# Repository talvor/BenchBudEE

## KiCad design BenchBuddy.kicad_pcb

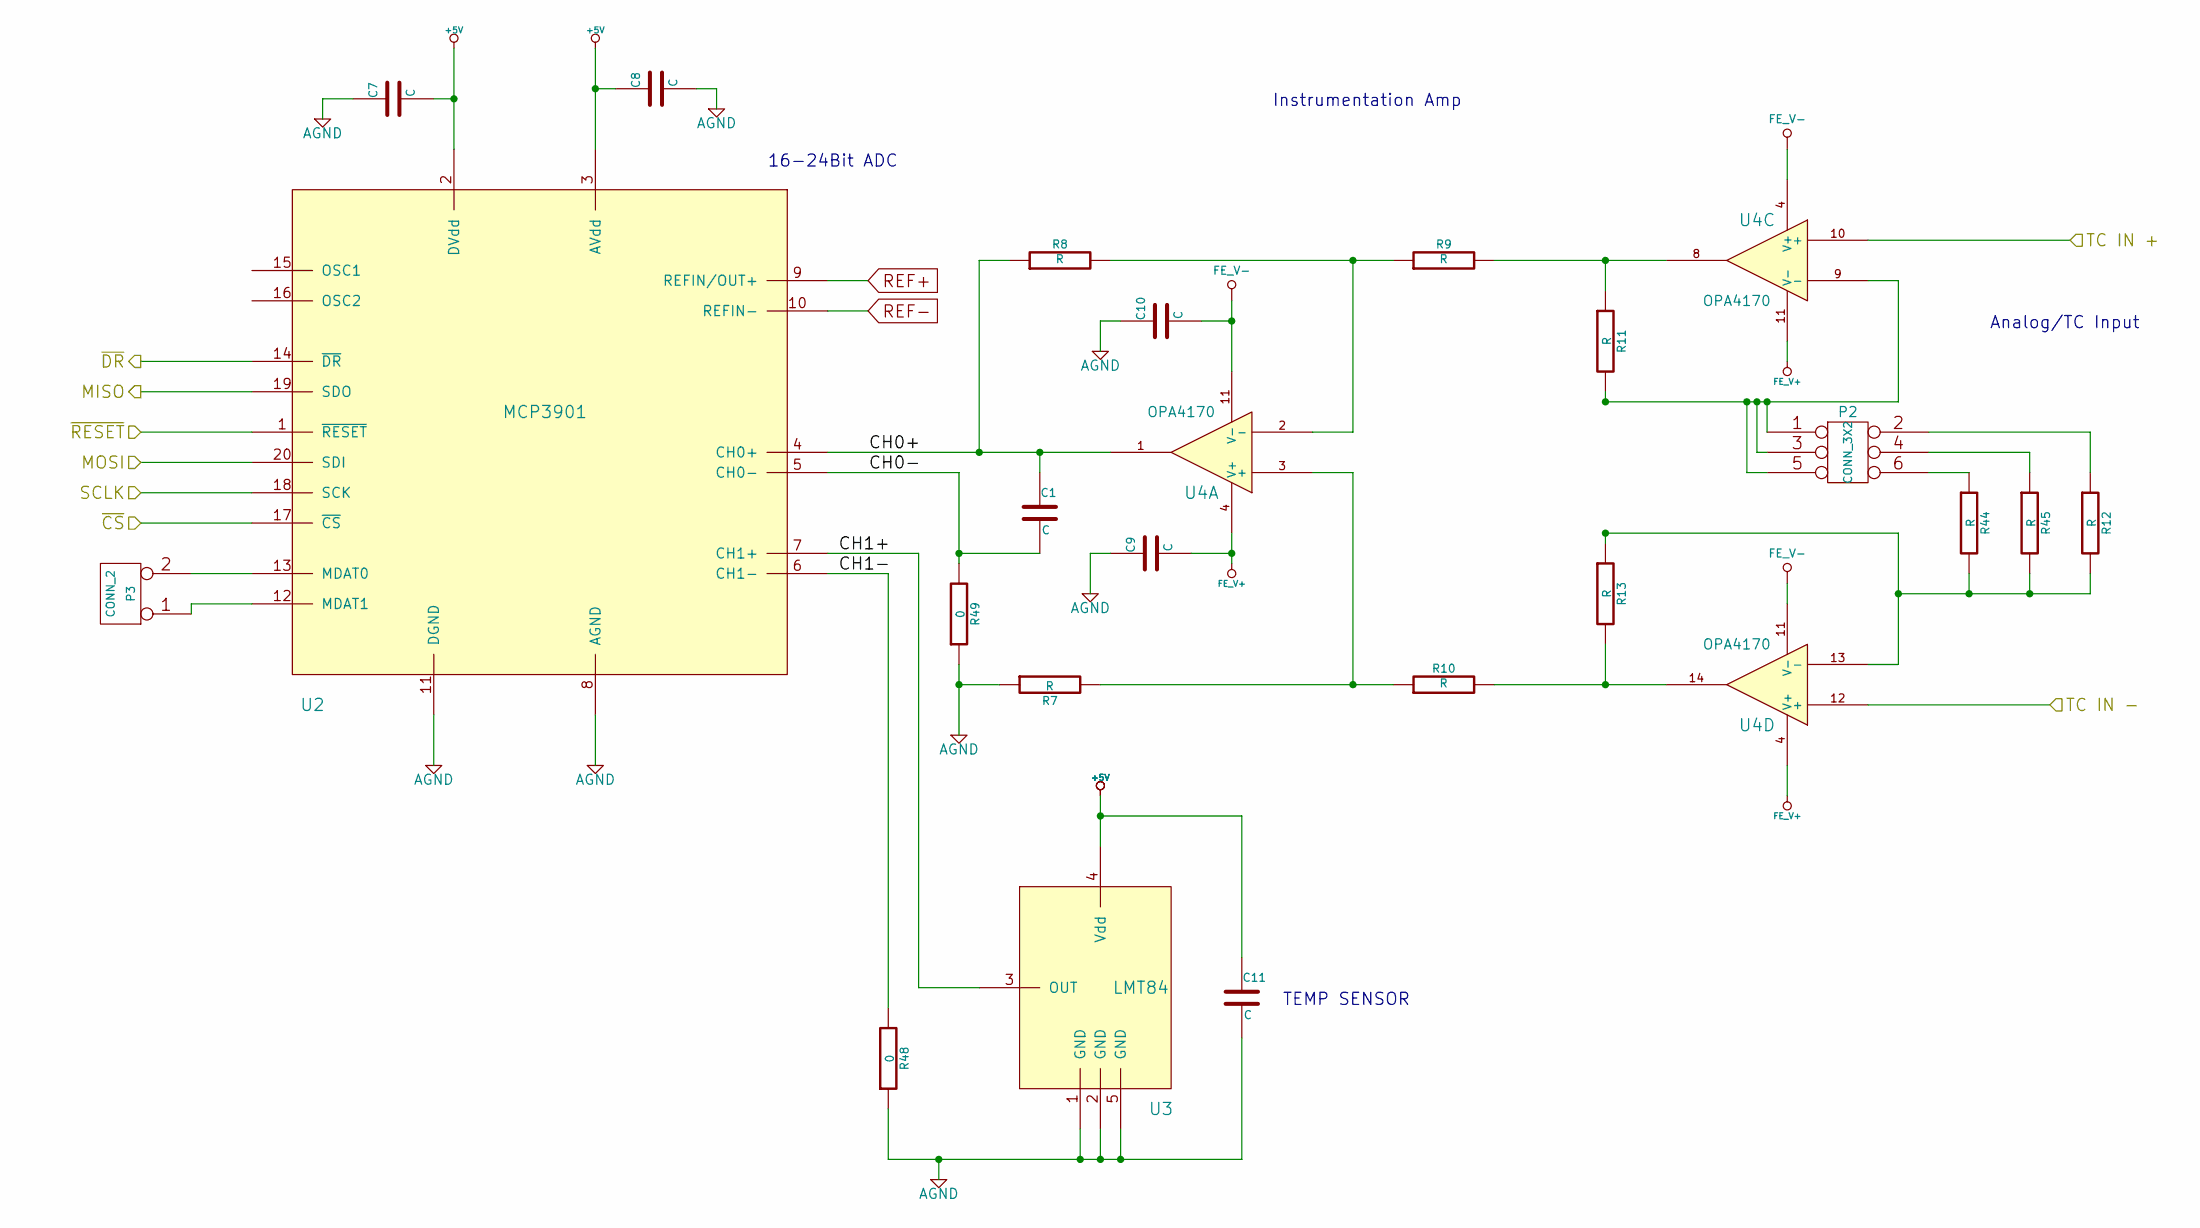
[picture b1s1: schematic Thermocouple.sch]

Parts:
C1, C7, C8, C9, C10, C11: C
P2: CONN_3X2
P3: CONN_2
R7, R8, R9, R10, R11, R12, R13, R44, R45: R
R48, R49: 0
U2: MCP3901
U3: LMT84
U4: OPA4170

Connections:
/Arduino/MISO: U2.19 (SDO); also elsewhere on the board
/Arduino/MOSI: U2.20 (SDI); also elsewhere on the board
/Arduino/SCLK: U2.18 (SCK); also elsewhere on the board
/Arduino/~ADC_CS: U2.17 (~CS); also elsewhere on the board
/Arduino/~DR: U2.14 (~DR); also elsewhere on the board
/Arduino/~RESET: U2.1 (~RESET); also elsewhere on the board
/Thermocouple/CH0+: C1.1, R8.1, U2.4 (CH0+), U4.1
/Thermocouple/CH0-: C1.2, R49.2, U2.5 (CH0-)
/Thermocouple/CH1+: U2.7 (CH1+), U3.3 (OUT)
/Thermocouple/CH1-: R48.2, U2.6 (CH1-)
/Thermocouple/TC IN +: U4.10 (+); also elsewhere on the board
/Thermocouple/TC IN -: U4.12 (+); also elsewhere on the board
AGND: C7.1, C8.2, C9.1, C10.1, C11.2, R7.1, R48.1, R49.1, U2.8 (AGND), U2.11 (DGND), U3.1 (GND), U3.2 (GND), U3.5 (GND); also elsewhere on the board
unnamed: P2.1, P2.3, P2.5, R11.2, U4.9 (-)
unnamed: P2.2, R12.1
unnamed: P2.4, R45.1
unnamed: P2.6, R44.1
unnamed: P3.1, U2.12 (MDAT1)
unnamed: P3.2 (PM), U2.13 (MDAT0)
unnamed: R8.2, R9.1, U4.2 (-)
unnamed: R7.2, R10.1, U4.3 (+)
unnamed: R10.2, R13.2, U4.14
unnamed: R9.2, R11.1, U4.8
unnamed: R12.2, R13.1, R44.2, R45.2, U4.13 (-)
REF+: U2.9 (REFIN/OUT+)
REF-: U2.10 (REFIN-)

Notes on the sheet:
Analog/TC Input
Instrumentation Amp
16-24Bit ADC
TEMP SENSOR

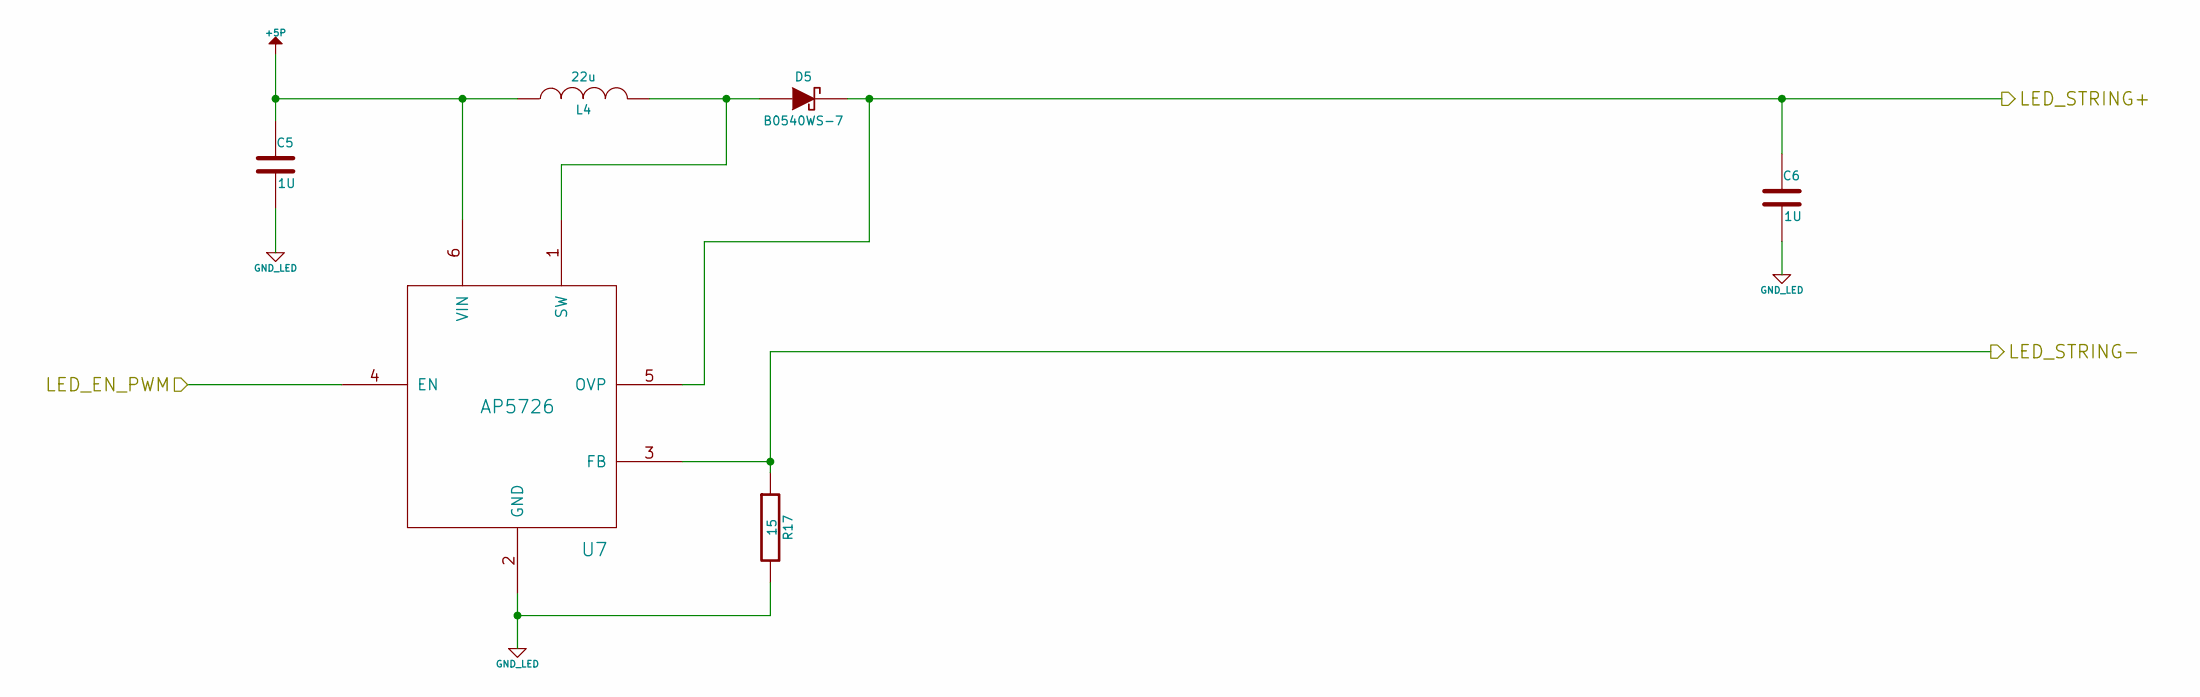
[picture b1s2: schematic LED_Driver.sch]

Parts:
C5, C6: 1U
D5: B0540WS-7
L4: 22u; MFG Part Number NR4012T220M
R17: 15
U7: AP5726

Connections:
+5P: C5.1, L4.1, U7.6 (VIN); also elsewhere on the board
/Arduino/LED_EN_PWM: U7.4 (EN); also elsewhere on the board
/LED_Driver/LED_STRING+: C6.1, D5.2 (K), U7.5 (OVP); also elsewhere on the board
/LED_Driver/LED_STRING-: R17.1, U7.3 (FB); also elsewhere on the board
GND_LED: C5.2, C6.2, R17.2, U7.2 (GND); also elsewhere on the board
unnamed: D5.1 (A), L4.2, U7.1 (SW)

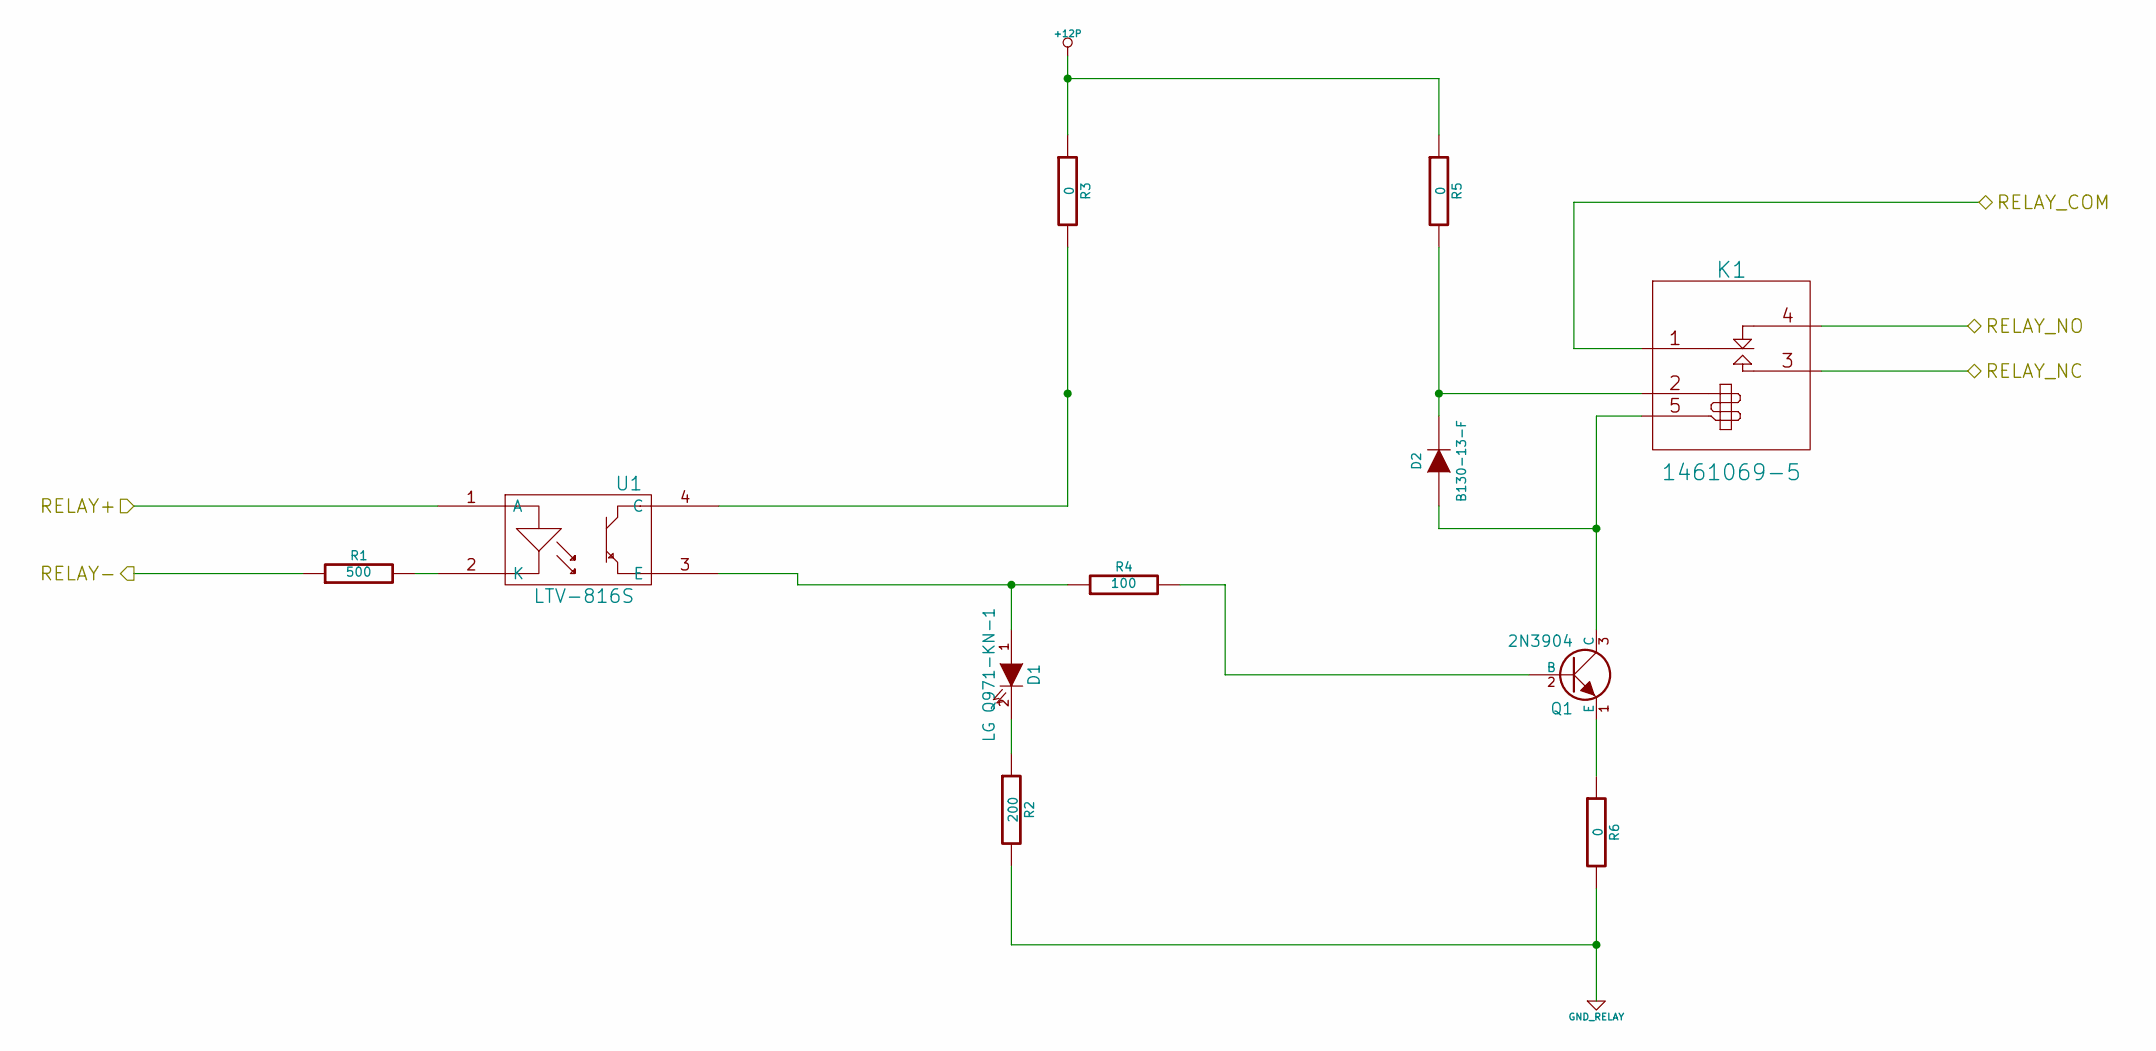
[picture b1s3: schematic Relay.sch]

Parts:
D1: LG Q971-KN-1
D2: B130-13-F
K1: 1461069-5
Q1: 2N3904; MFG Part Number MMBT3904-7-F
R1: 500
R2: 200
R3, R5, R6: 0
R4: 100
U1: LTV-816S; MFG Part Number LTV-816S

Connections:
+12P: R3.1, R5.1; also elsewhere on the board
/Arduino/RELAY+: U1.1 (A); also elsewhere on the board
/Arduino/RELAY-: R1.1; also elsewhere on the board
/Relay/RELAY_COM: K1.1 (COM); also elsewhere on the board
/Relay/RELAY_NC: K1.3 (NO); also elsewhere on the board
/Relay/RELAY_NO: K1.4 (NC); also elsewhere on the board
GND_RELAY: R2.2, R6.2; also elsewhere on the board
unnamed: D1.1 (A), R4.1, U1.3 (E)
unnamed: D1.2 (K), R2.1
unnamed: D2.1 (A), K1.5 (COIL-), Q1.3 (C)
unnamed: D2.2 (K), K1.2 (COIL+), R5.2
unnamed: Q1.1 (E), R6.1
unnamed: Q1.2 (B), R4.2
unnamed: R1.2, U1.2 (K)
unnamed: R3.2, U1.4 (C)

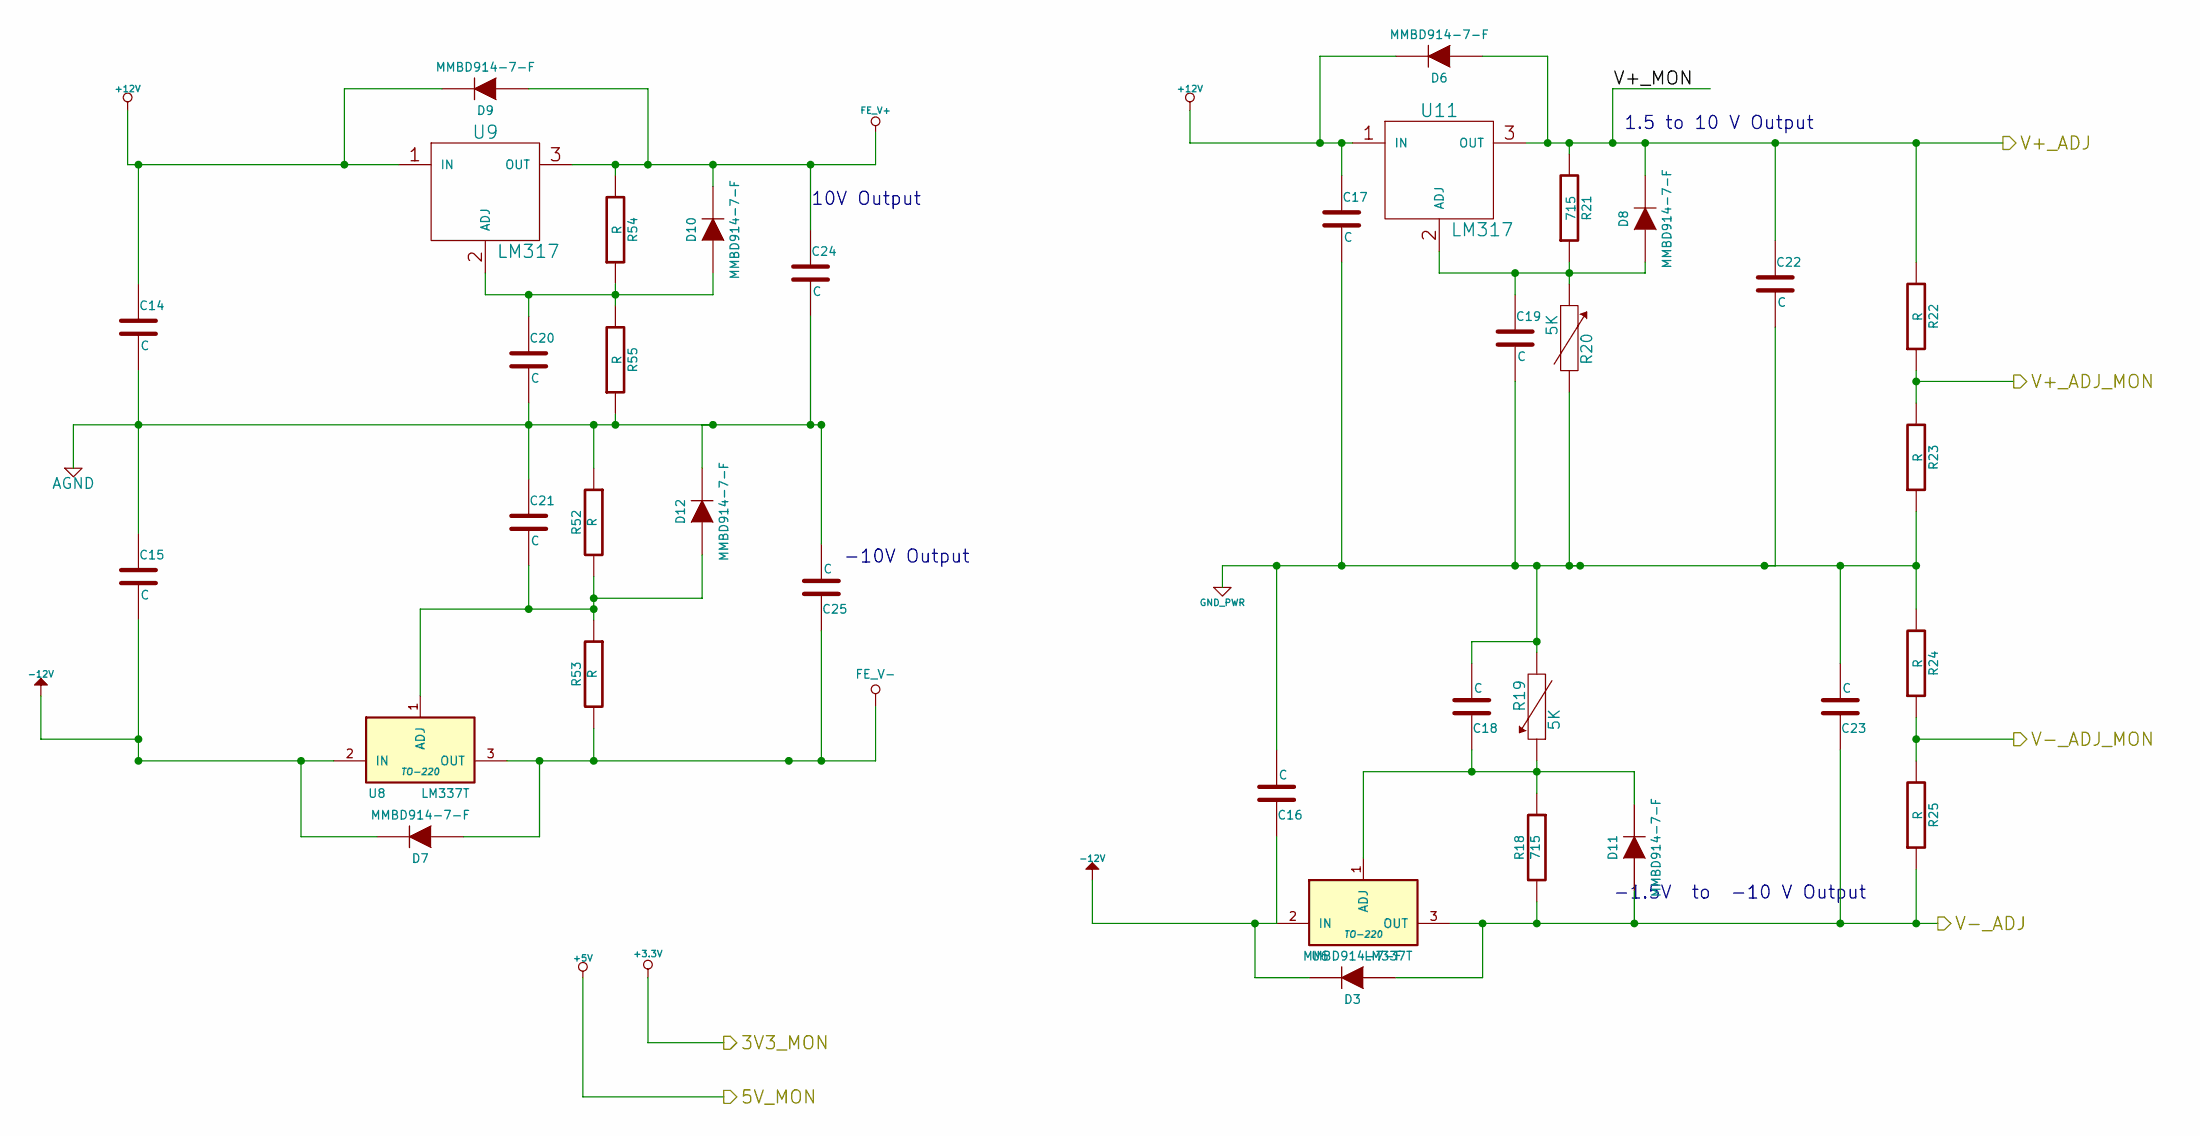
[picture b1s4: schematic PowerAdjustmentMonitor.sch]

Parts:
C14, C15, C16, C17, C18, C19, C20, C21, C22, C23, C24, C25: C
D3, D6, D7, D8, D9, D10, D11, D12: MMBD914-7-F
R18, R21: 715
R19, R20: 5K
R22, R23, R24, R25, R52, R53, R54, R55: R
U6, U8: LM337T; TO-220
U9, U11: LM317

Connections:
+12V: C14.1, C17.1, D6.2 (K), D9.2 (K), U9.1 (IN), U11.1 (IN); also elsewhere on the board
-12V: C15.2, C16.1, D3.2 (K), D7.2 (K), U6.2 (IN), U8.2 (IN); also elsewhere on the board
/Arduino/V+_ADJ_MON: R22.1, R23.2; also elsewhere on the board
/Arduino/V-_ADJ_MON: R24.1, R25.2; also elsewhere on the board
/PowerAdjustmentMonitor/V+_ADJ: C22.1, D6.1 (A), D8.2 (K), R21.2, R22.2, U11.3 (OUT); also elsewhere on the board
/PowerAdjustmentMonitor/V-_ADJ: C23.1, D3.1 (A), D11.1 (A), R18.2, R25.1, U6.3 (OUT); also elsewhere on the board
AGND: C14.2, C15.1, C20.2, C21.1, C24.2, C25.2, D12.2 (K), R52.1, R55.1; also elsewhere on the board
GND_PWR: C16.2, C17.2, C18.2, C19.2, C22.2, C23.2, R19.2, R20.2, R23.1, R24.2; also elsewhere on the board
unnamed: C18.1, D11.2 (K), R18.1, R19.1, U6.1 (ADJ)
unnamed: C19.1, D8.1 (A), R20.1, R21.1, U11.2 (ADJ)
unnamed: C20.1, D10.1 (A), R54.1, R55.2, U9.2 (ADJ)
unnamed: C21.2, D12.1 (A), R52.2, R53.1, U8.1 (ADJ)

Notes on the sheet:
10V Output
1.5 to 10 V Output
-10V Output
-1.5V to -10 V Output

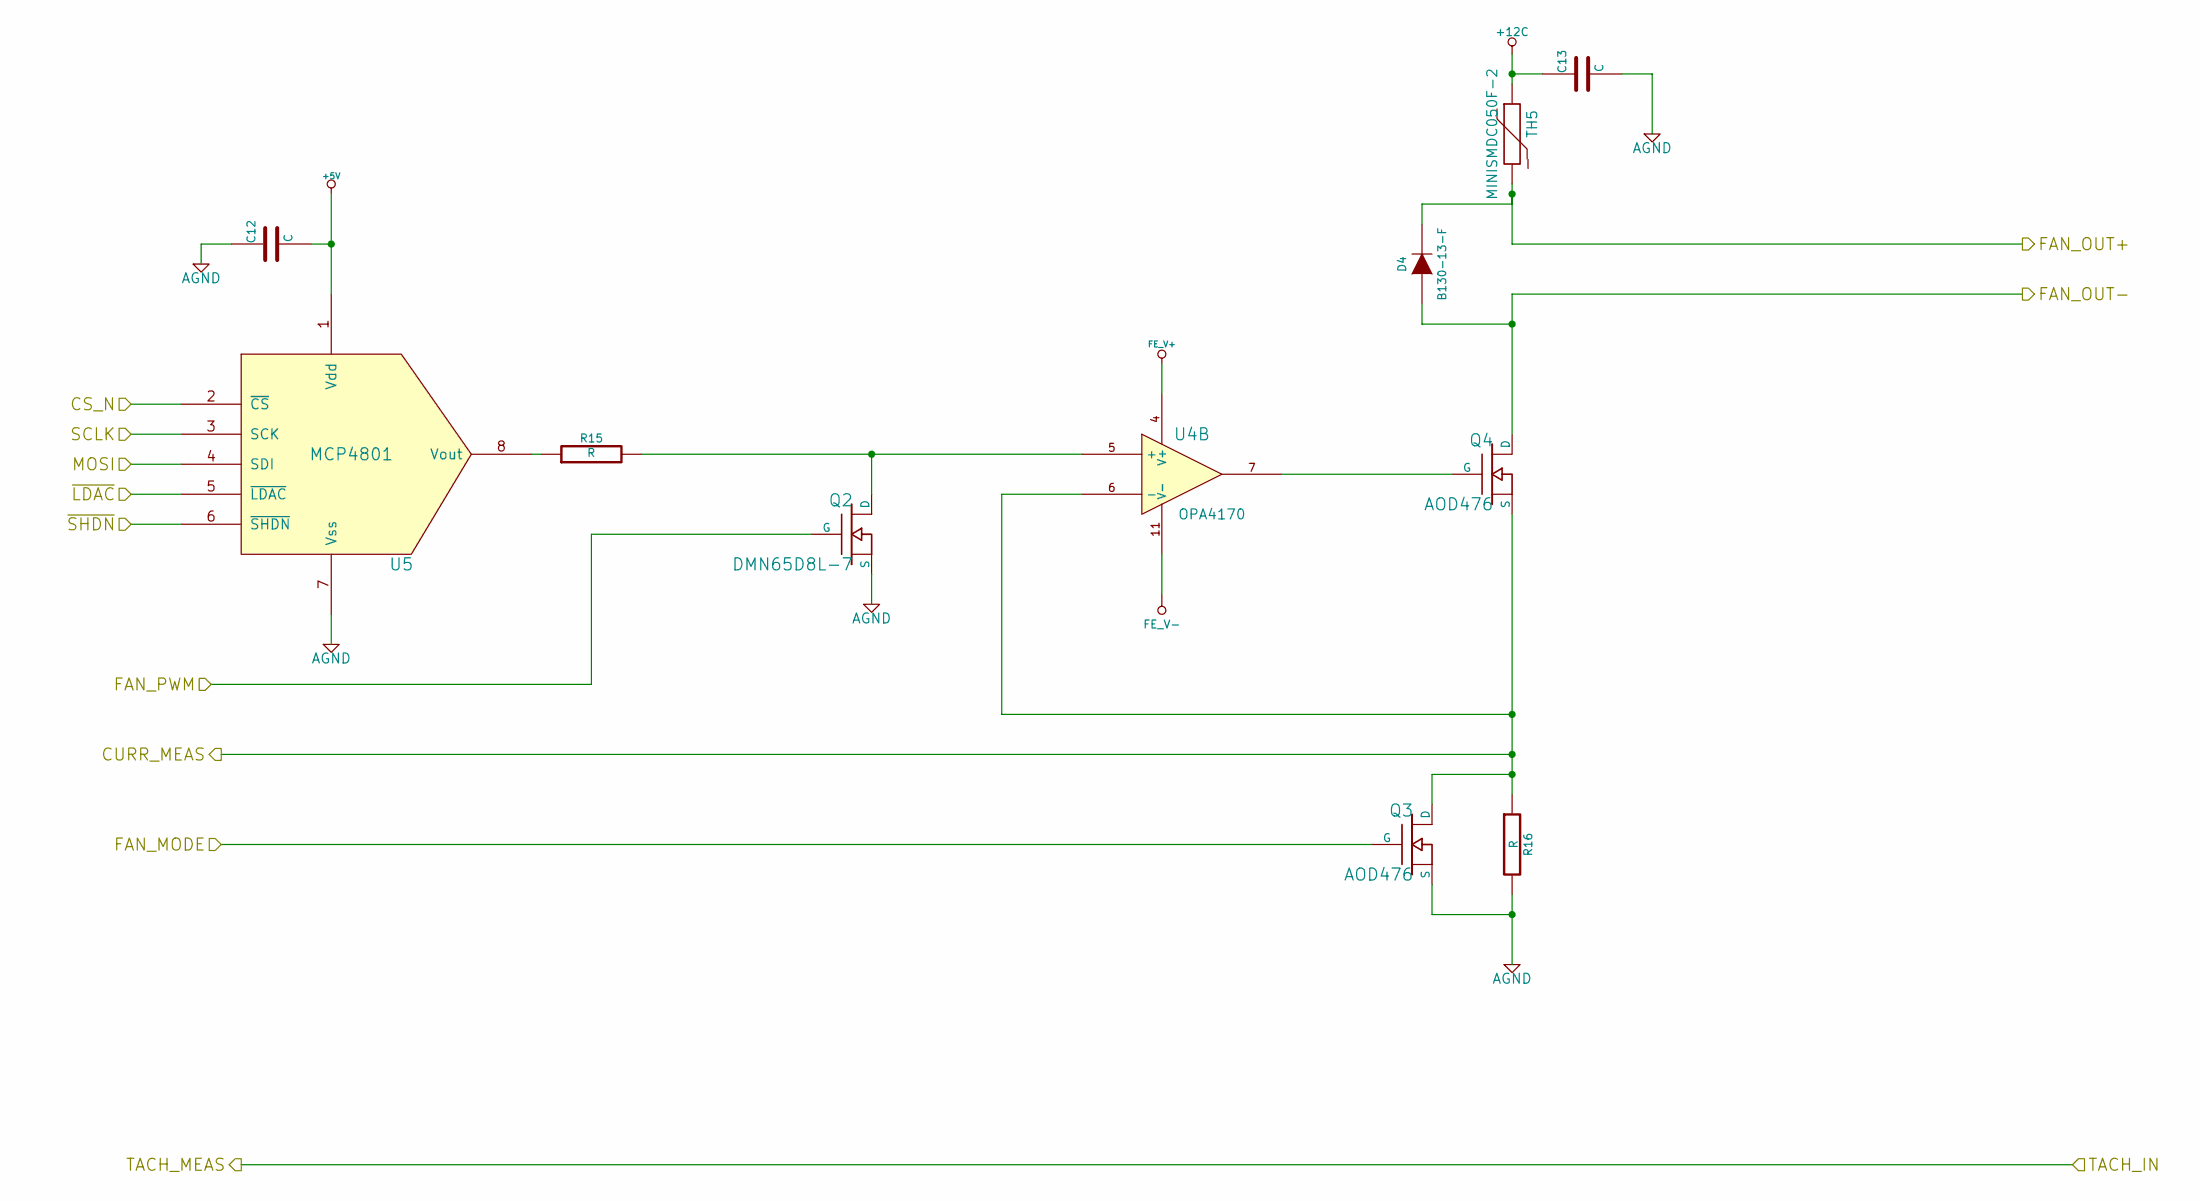
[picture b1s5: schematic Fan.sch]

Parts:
C12, C13: C
D4: B130-13-F; MFG Part Number B130-13-F
Q2: DMN65D8L-7; MFG Part Number DMN65D8L-7
Q3, Q4: AOD476; MFG Part Number AOD476
R15, R16: R
TH5: MINISMDC050F-2; MFG Part Number MINISMDC050F-2
U4: OPA4170
U5: MCP4801

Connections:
+12C: C13.1, TH5.1; also elsewhere on the board
/Arduino/CURR_MEAS: Q3.2 (D), Q4.3 (S), R16.1, U4.6 (-); also elsewhere on the board
/Arduino/FAN_MODE: Q3.1 (G); also elsewhere on the board
/Arduino/FAN_PWM: Q2.G; also elsewhere on the board
/Arduino/MOSI: U5.4 (SDI); also elsewhere on the board
/Arduino/SCLK: U5.3 (SCK); also elsewhere on the board
/Arduino/~LDAC: U5.5 (~LDAC); also elsewhere on the board
/Arduino/~SHDN: U5.6 (~SHDN); also elsewhere on the board
/Fan/CS_N: U5.2 (~CS); also elsewhere on the board
/Fan/FAN_OUT+: D4.2 (K), TH5.2; also elsewhere on the board
/Fan/FAN_OUT-: D4.1 (A), Q4.2 (D); also elsewhere on the board
AGND: C12.1, C13.2, Q2.3 (S), Q2.S, Q3.3 (S), R16.2, U5.7 (Vss); also elsewhere on the board
unnamed: Q2.2 (D), Q2.D, R15.2, U4.5 (+)
unnamed: Q4.1 (G), U4.7
unnamed: R15.1, U5.8 (Vout)

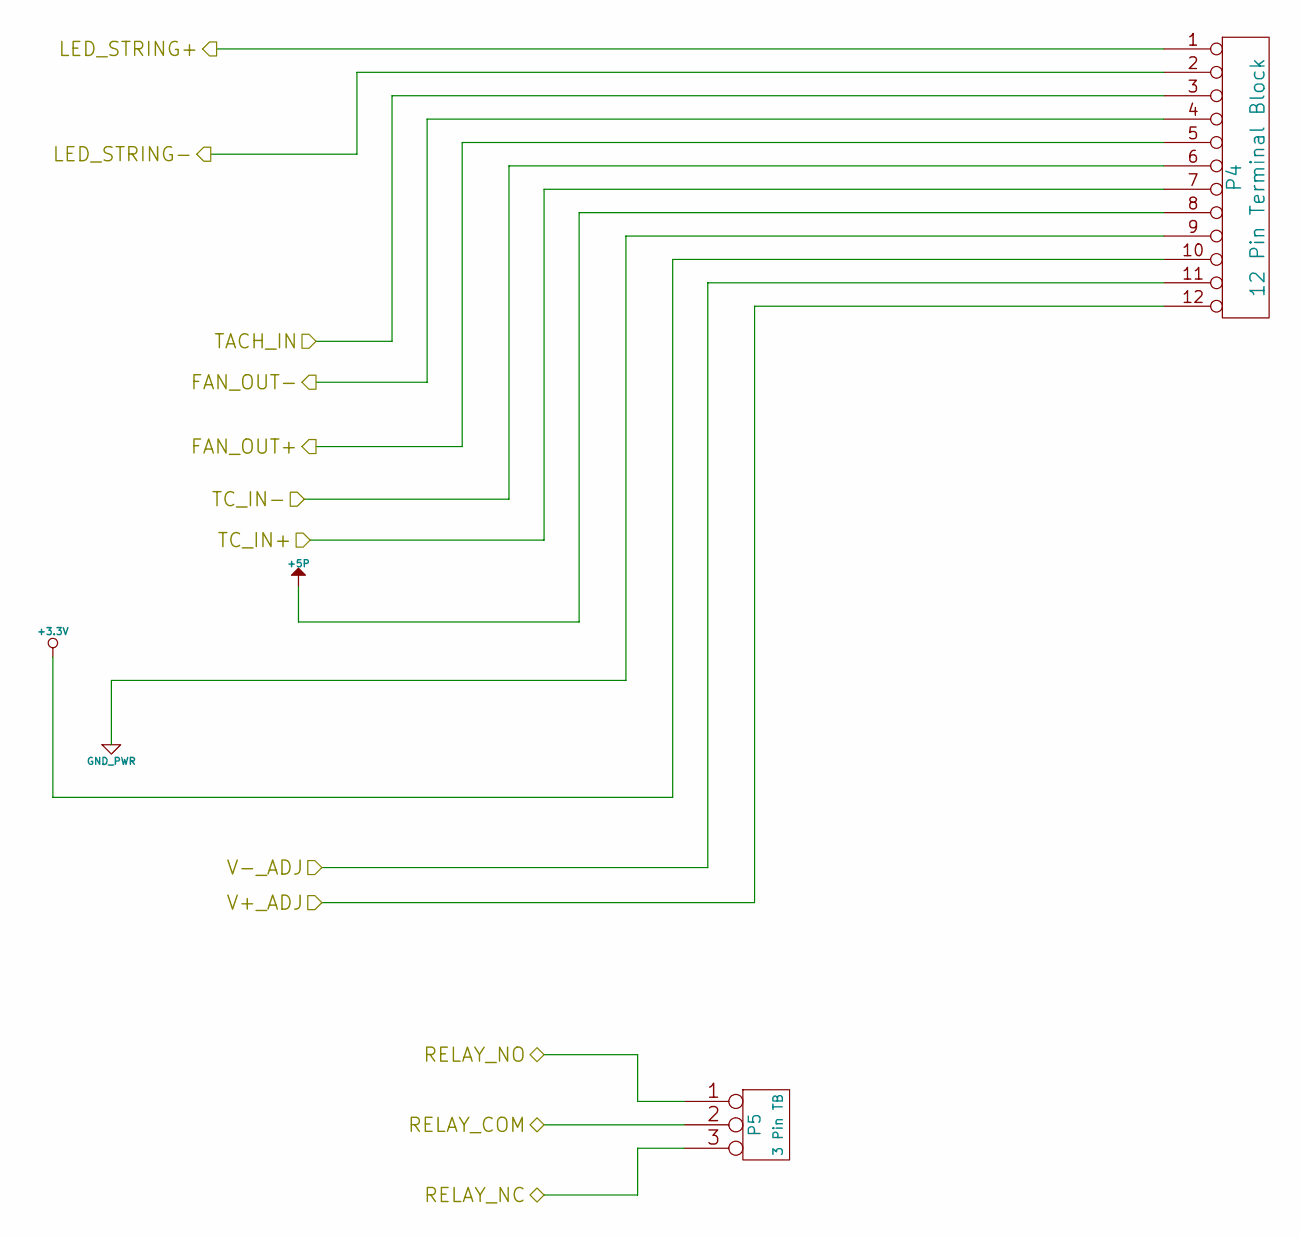
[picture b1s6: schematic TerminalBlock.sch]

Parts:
P4: 12 Pin Terminal Block; MFG Part Number OSTTE120104
P5: 3 Pin TB; MFG Part Number 1935174

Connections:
+3.3V: P4.10; also elsewhere on the board
+5P: P4.8; also elsewhere on the board
/Fan/FAN_OUT+: P4.5; also elsewhere on the board
/Fan/FAN_OUT-: P4.4; also elsewhere on the board
/Fan/TACH_IN: P4.3; also elsewhere on the board
/LED_Driver/LED_STRING+: P4.1; also elsewhere on the board
/LED_Driver/LED_STRING-: P4.2; also elsewhere on the board
/PowerAdjustmentMonitor/V+_ADJ: P4.12; also elsewhere on the board
/PowerAdjustmentMonitor/V-_ADJ: P4.11; also elsewhere on the board
/Relay/RELAY_COM: P5.2 (PM); also elsewhere on the board
/Relay/RELAY_NC: P5.3; also elsewhere on the board
/Relay/RELAY_NO: P5.1; also elsewhere on the board
/Thermocouple/TC IN +: P4.6; also elsewhere on the board
/Thermocouple/TC IN -: P4.7; also elsewhere on the board
GND_PWR: P4.9; also elsewhere on the board

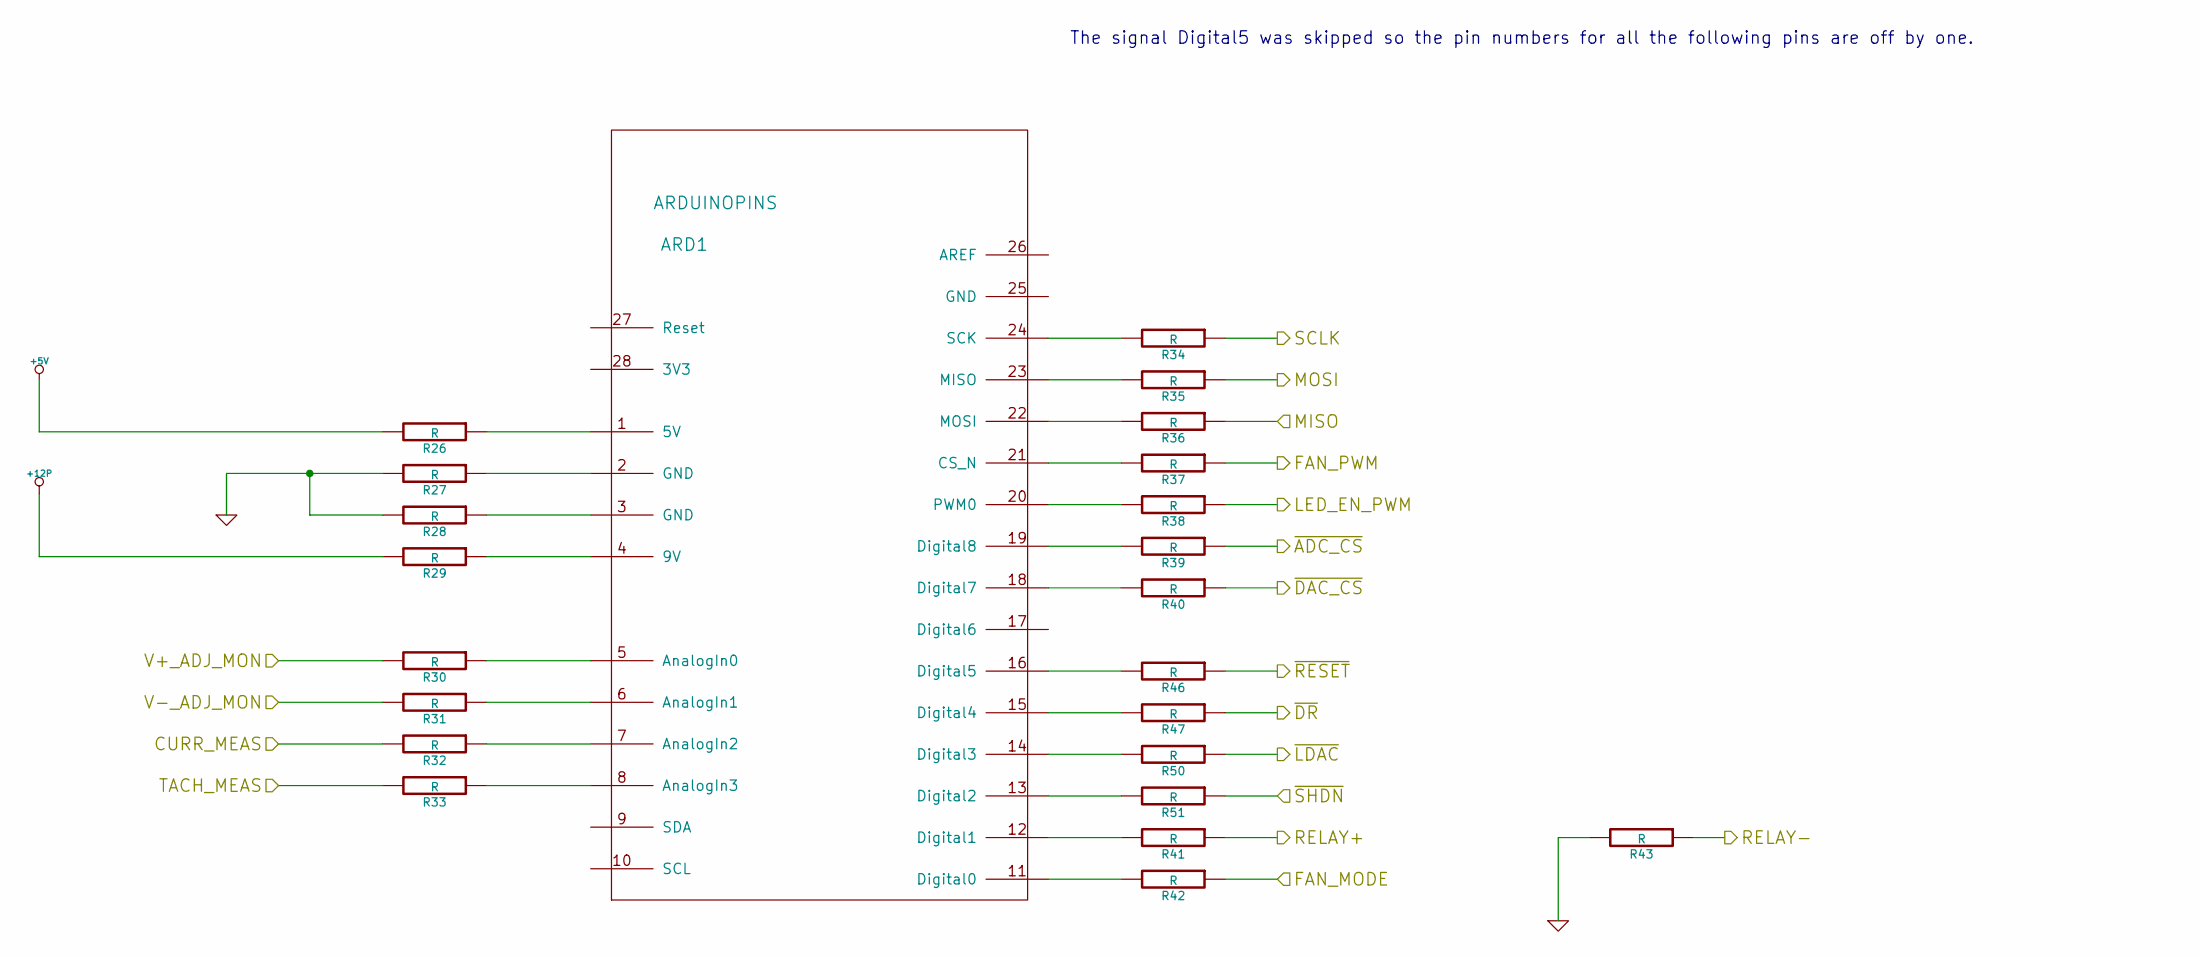
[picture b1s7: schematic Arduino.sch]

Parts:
ARD1: ARDUINOPINS
R26, R27, R28, R29, R30, R31, R32, R33, R34, R35, R36, R37, R38, R39, R40, R41, R42, R43, R46, R47, R50, R51: R

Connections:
+12P: R29.2; also elsewhere on the board
/Arduino/CURR_MEAS: R32.2; also elsewhere on the board
/Arduino/FAN_MODE: R42.1; also elsewhere on the board
/Arduino/FAN_PWM: R37.1; also elsewhere on the board
/Arduino/LED_EN_PWM: R38.1; also elsewhere on the board
/Arduino/MISO: R36.1; also elsewhere on the board
/Arduino/MOSI: R35.1; also elsewhere on the board
/Arduino/RELAY+: R41.1; also elsewhere on the board
/Arduino/RELAY-: R43.1; also elsewhere on the board
/Arduino/SCLK: R34.1; also elsewhere on the board
/Arduino/V+_ADJ_MON: R30.2; also elsewhere on the board
/Arduino/V-_ADJ_MON: R31.2; also elsewhere on the board
/Arduino/~ADC_CS: R39.1; also elsewhere on the board
/Arduino/~DR: R47.1; also elsewhere on the board
/Arduino/~LDAC: R50.1; also elsewhere on the board
/Arduino/~RESET: R46.1; also elsewhere on the board
/Arduino/~SHDN: R51.1; also elsewhere on the board
/Fan/CS_N: R40.1; also elsewhere on the board
/Fan/TACH_IN: R33.2; also elsewhere on the board
GND: R27.2, R28.2, R43.2; also elsewhere on the board
unnamed: ARD1.1 (5V), R26.1
unnamed: ARD1.2 (GND), R27.1
unnamed: ARD1.3 (GND), R28.1
unnamed: ARD1.4 (9V), R29.1
unnamed: ARD1.5 (AnalogIn0), R30.1
unnamed: ARD1.6 (AnalogIn1), R31.1
unnamed: ARD1.7 (AnalogIn2), R32.1
unnamed: ARD1.8 (AnalogIn3), R33.1
unnamed: ARD1.11 (Digital0), R42.2
unnamed: ARD1.13 (Digital2), R51.2
unnamed: ARD1.14 (Digital3), R50.2
unnamed: ARD1.15 (Digital4), R47.2
unnamed: ARD1.16 (Digital5), R46.2
unnamed: ARD1.18 (Digital7), R40.2
unnamed: ARD1.19 (Digital8), R39.2
unnamed: ARD1.20 (PWM0), R38.2
unnamed: ARD1.21 (CS_N), R37.2
unnamed: ARD1.22 (MOSI), R36.2
unnamed: ARD1.23 (MISO), R35.2
unnamed: ARD1.24 (SCK), R34.2

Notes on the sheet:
The signal Digital5 was skipped so the pin numbers for all the following pins are off by one.
